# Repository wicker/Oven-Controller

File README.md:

# Composites Curing Oven Controller

For the composites oven team at Portland State. 

v0 - the original schematic representation of the current working breadboard setup.  
v1 - the finished Arduino shield version on a printed circuit board. this works!  
v2 - additions to the v1 Arduino shield design.  
v3 - developing final version for OSHPark order.

**Note**  
On March 6th the oven controller is now being worked on in the mme-capstone repo in the PSAS organization: https://github.com/psas/mme-capstone

### Version 3

v3 is the final version of the oven controller installed on a 4’×8’×4’ curing oven at Portland State in the Mechanical Engineering department.

The blue case is 3D-printed and gets attached to the side of the oven. The electronics are a three-board stack with an Arduino Uno R3 on the bottom; a custom oven control board set up in the middle with screw-in Euroterminals for start switch, relay, and thermocouple wires; and a 1.8” TFT LCD Shield from Adafruit for the display on top.

The display allows the user to program up to nine steps in a temperature profile. Each step lets the user specify a ramp rate, hold temperature, and hold time. Once all the steps are set, the user should set the relay enable switch to ON and then tell the program to begin running the profile.

The program automatically detects which thermocouples are present and uses the temperature as input to a PID loop which controls ramp rate by turning on and off up to four relays which are, for our configuration, controlling two heaters, one fan, and one vent.

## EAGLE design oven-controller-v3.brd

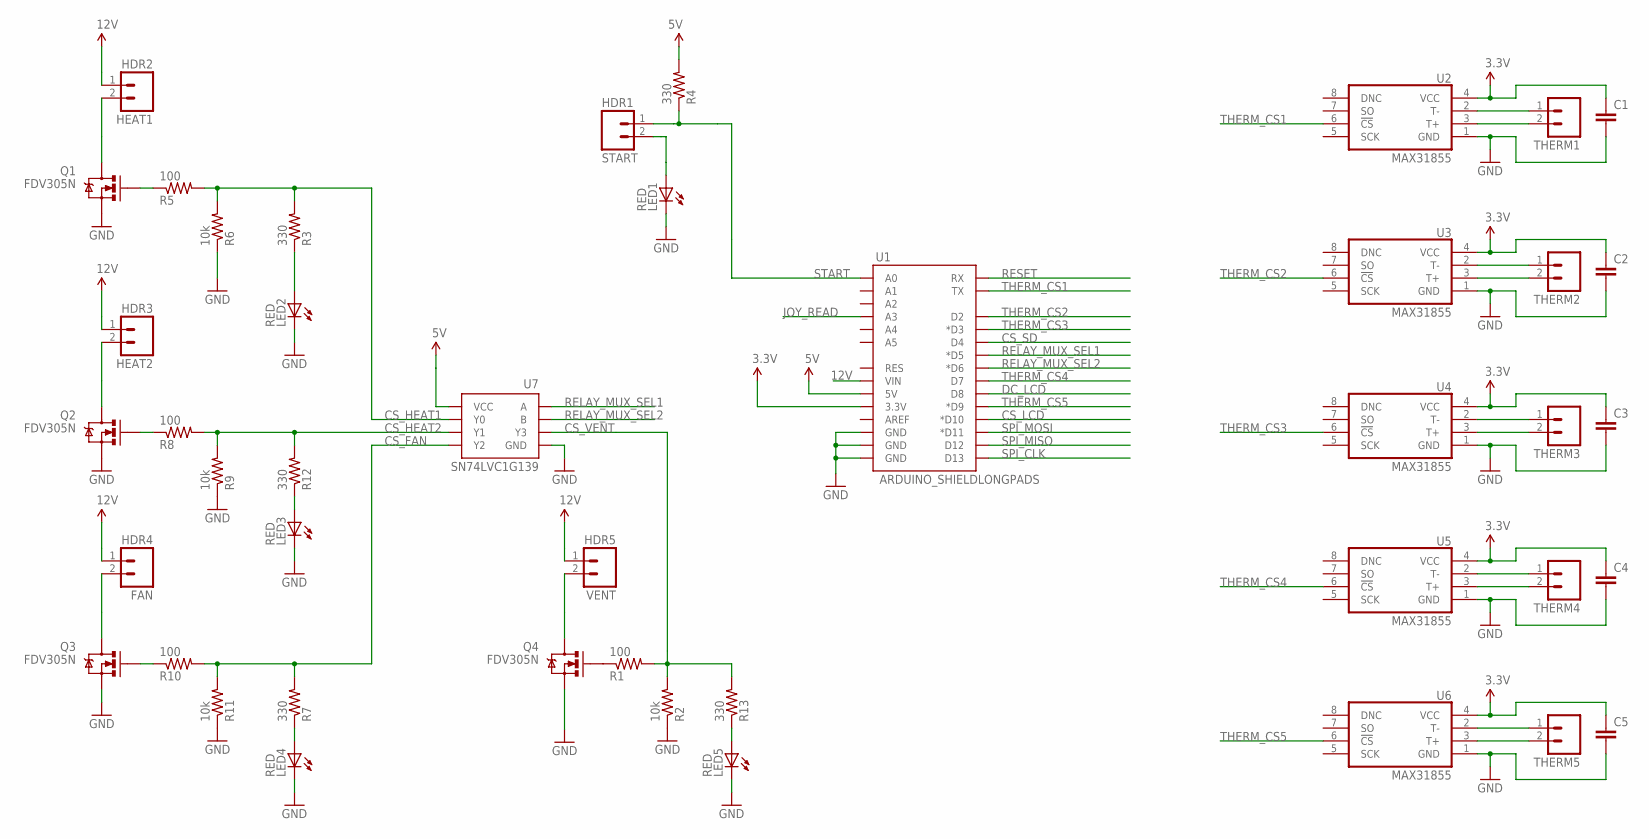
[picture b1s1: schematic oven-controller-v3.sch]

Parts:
C1, C2, C3, C4, C5: C-EUC0603K; C0603K
FAN: HDR4; SCREWTERMINAL-3.5MM-2_LOCK
HEAT1: HDR2; SCREWTERMINAL-3.5MM-2_LOCK
HEAT2: HDR3; SCREWTERMINAL-3.5MM-2_LOCK
LED1, LED2, LED3, LED4, LED5: RED; LED-0603
Q1, Q2, Q3, Q4: FDV305N; SOT23-3
R1, R5, R8, R10: 100; 0603-C-NOSILK
R2, R6, R9, R11: 10k; 0603-C-NOSILK
R3, R4, R7, R12, R13: 330; 0603-C-NOSILK
START: HDR1; SCREWTERMINAL-3.5MM-2_LOCK
THERM1, THERM2, THERM3, THERM4, THERM5: M023.5MM_LOCK; SCREWTERMINAL-3.5MM-2_LOCK
U1: ARDUINO_SHIELDLONGPADS; DUEMILANOVE_SHIELD_LONGPADS
U2, U3, U4, U5, U6: MAX31855; SO-8
U7: SN74LVC1G139; 8LSSOP
VENT: HDR5; SCREWTERMINAL-3.5MM-2_LOCK

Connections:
3.3V: C1.1, C2.1, C3.1, C4.1, C5.1, U1.3.3V, U2.4 (VCC), U3.4 (VCC), U4.4 (VCC), U5.4 (VCC), U6.4 (VCC)
5V: R4.2, U1.5V, U7.P$8 (VCC)
12V: FAN.1, HEAT1.1, HEAT2.1, U1.VIN, VENT.1
CS_FAN: R7.2, R10.2, R11.2, U7.P$5 (Y2)
CS_HEAT1: R3.2, R5.2, R6.2, U7.P$7 (Y0)
CS_HEAT2: R8.2, R9.2, R12.2, U7.P$6 (Y1)
CS_LCD: U1.D10 (*D10)
CS_SD: U1.D4
CS_VENT: R1.2, R2.2, R13.2, U7.P$3 (Y3)
DC_LCD: U1.D8
GND: C1.2, C2.2, C3.2, C4.2, C5.2, LED1.C, LED2.C, LED3.C, LED4.C, LED5.C, Q1.2 (S), Q2.2 (S), Q3.2 (S), Q4.2 (S), R2.1, R6.1, R9.1, R11.1, U1.GND@0 (GND), U1.GND@1 (GND), U1.GND@2 (GND), U2.1 (GND), U3.1 (GND), U4.1 (GND), U5.1 (GND), U6.1 (GND), U7.P$4 (GND)
HDR3: FAN.2, Q3.3 (D)
JOY_READ: U1.A3
unnamed: Q1.1 (G), R5.1
unnamed: Q4.1 (G), R1.1
unnamed: Q4.3 (D), VENT.2
unnamed: HEAT1.2, Q1.3 (D)
unnamed: THERM1.1, U2.2 (T-)
unnamed: THERM1.2, U2.3 (T+)
unnamed: LED2.A, R3.1
unnamed: THERM2.1, U3.2 (T-)
unnamed: LED4.A, R7.1
unnamed: LED1.A, START.2
unnamed: THERM2.2, U3.3 (T+)
unnamed: THERM3.1, U4.2 (T-)
unnamed: THERM3.2, U4.3 (T+)
unnamed: THERM4.1, U5.2 (T-)
unnamed: THERM4.2, U5.3 (T+)
unnamed: THERM5.1, U6.2 (T-)
unnamed: THERM5.2, U6.3 (T+)
unnamed: LED3.A, R12.1
unnamed: LED5.A, R13.1
unnamed: Q2.1 (G), R8.1
unnamed: HEAT2.2, Q2.3 (D)
unnamed: Q3.1 (G), R10.1
RELAY_MUX_SEL1: U1.D5 (*D5), U7.P$1 (A)
RELAY_MUX_SEL2: U1.D6 (*D6), U7.P$2 (B)
RESET: U1.RX
SPI_CLK: U1.D13
SPI_MISO: U1.D12
SPI_MOSI: U1.D11 (*D11)
START: R4.1, START.1, U1.A0
THERM_CS1: U1.TX, U2.6 (!CS)
THERM_CS2: U1.D2, U3.6 (!CS)
THERM_CS3: U1.D3 (*D3), U4.6 (!CS)
THERM_CS4: U1.D7, U5.6 (!CS)
THERM_CS5: U1.D9 (*D9), U6.6 (!CS)

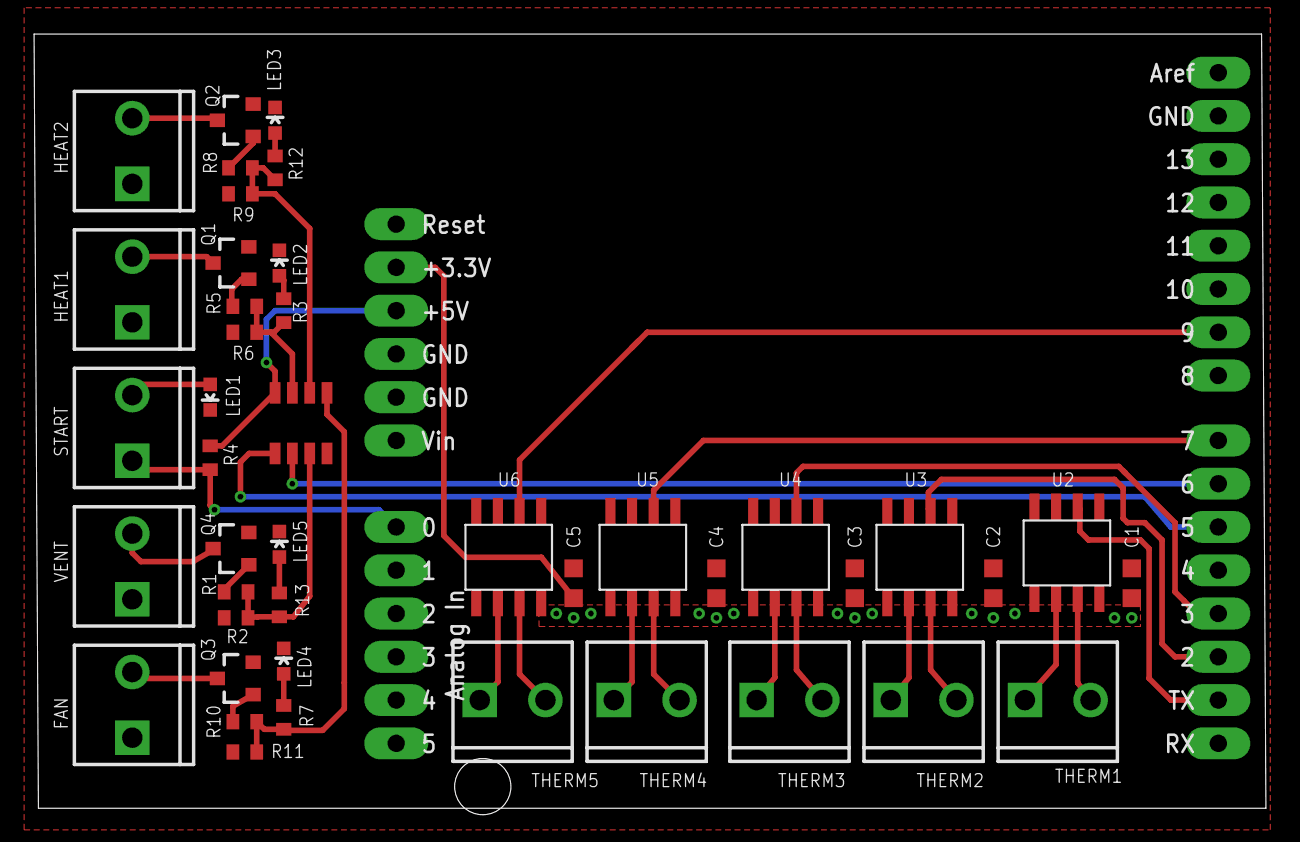
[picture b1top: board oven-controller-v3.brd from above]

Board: 2 copper layers, 72.3 x 45.4 mm, 44 parts (0 on the bottom side), 39 nets.

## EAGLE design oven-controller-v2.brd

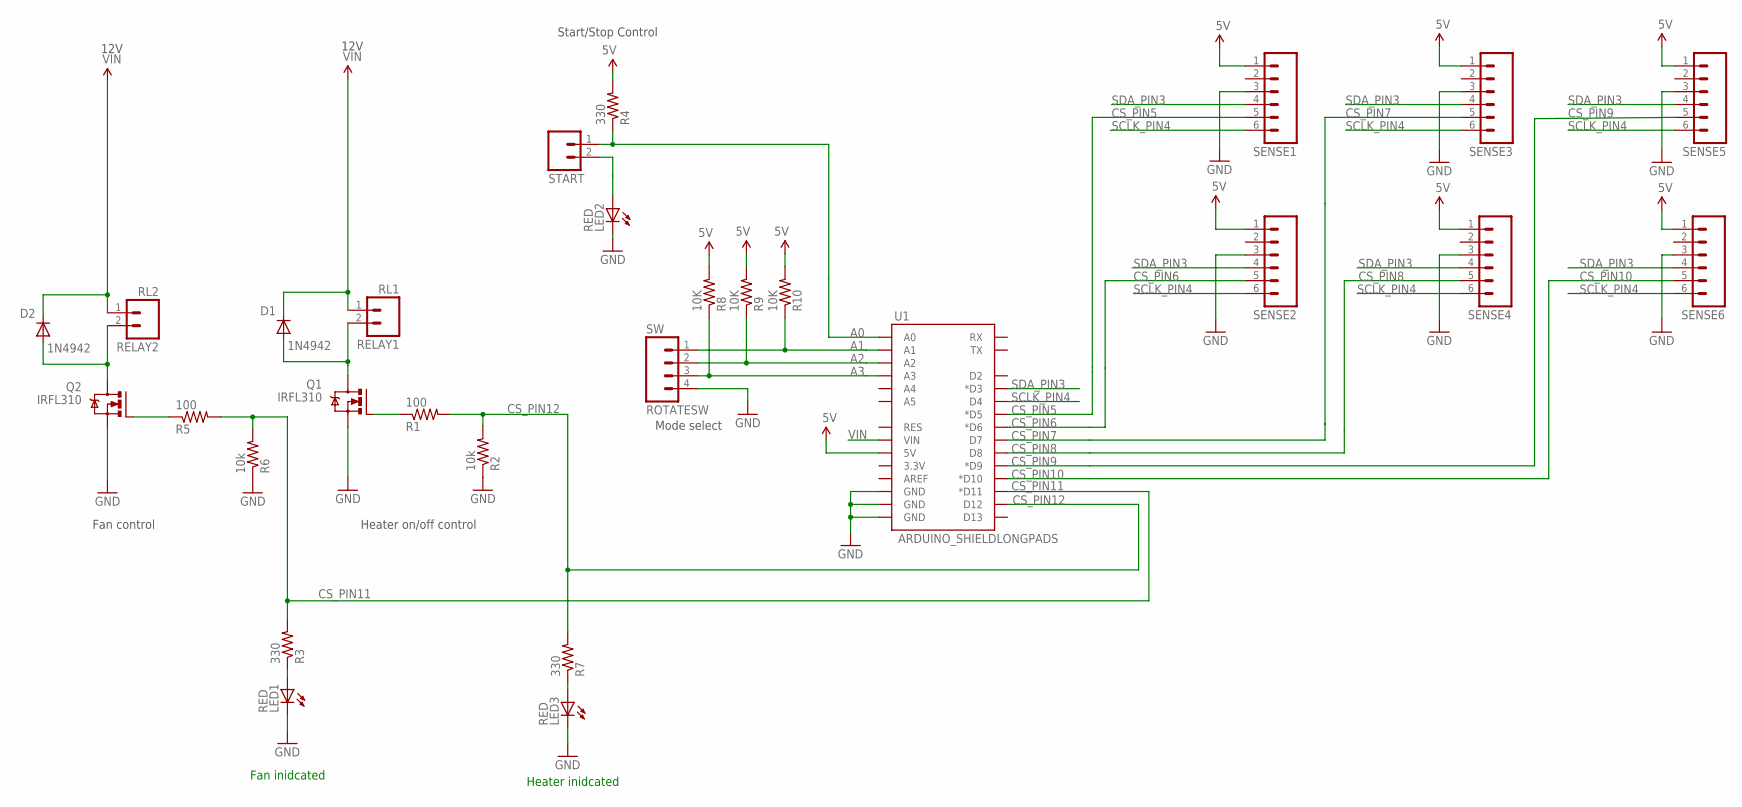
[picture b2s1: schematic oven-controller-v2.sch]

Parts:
D1, D2: 1N4942; DO41-10
LED1, LED2, LED3: RED; LED5MM
Q1, Q2: IRFL310; TO220BV
R1, R5: 100; AXIAL-0.3
R2, R6: 10k; AXIAL-0.3
R3, R4, R7: 330; AXIAL-0.3
R8, R9, R10: 10K; AXIAL-0.3
RELAY1: RL1; SCREWTERMINAL-3.5MM-2_LOCK
RELAY2: RL2; SCREWTERMINAL-3.5MM-2_LOCK
ROTATESW: SW; 1X04_LOCK_LONGPADS
SENSE1, SENSE2, SENSE3, SENSE4, SENSE5, SENSE6: M06LOCK_LONGPADS; 1X06_LOCK_LONGPADS
START: M023.5MM_LOCK; SCREWTERMINAL-3.5MM-2_LOCK
U1: ARDUINO_SHIELDLONGPADS; DUEMILANOVE_SHIELD_LONGPADS

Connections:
5V: R4.P$2 (2), R8.P$2 (2), R9.P$2 (2), R10.P$2 (2), SENSE1.1, SENSE2.1, SENSE3.1, SENSE4.1, SENSE5.1, SENSE6.1, U1.5V
A0: R4.P$1 (1), START.1, U1.A0
A1: R10.P$1 (1), ROTATESW.1, U1.A1
A2: R9.P$1 (1), ROTATESW.2, U1.A2
A3: R8.P$1 (1), ROTATESW.3, U1.A3
CCO: SENSE1.4, SENSE2.4, SENSE3.4, SENSE4.4, SENSE5.4, SENSE6.4, U1.D3 (*D3)
CS_PIN5: SENSE1.5, U1.D5 (*D5)
CS_PIN6: SENSE2.5, U1.D6 (*D6)
CS_PIN7: SENSE3.5, U1.D7
CS_PIN8: SENSE4.5, U1.D8
CS_PIN9: SENSE5.5, U1.D9 (*D9)
CS_PIN10: SENSE6.5, U1.D10 (*D10)
CS_PIN11: R3.P$2 (2), R5.P$2 (2), R6.P$2 (2), U1.D11 (*D11)
CS_PIN12: R1.P$2 (2), R2.P$2 (2), R7.P$2 (2), U1.D12
GND: LED1.K (C), LED2.K (C), LED3.K (C), Q1.S, Q2.S, R2.P$1 (1), R6.P$1 (1), ROTATESW.4, SENSE1.3, SENSE2.3, SENSE3.3, SENSE4.3, SENSE5.3, SENSE6.3, U1.GND@0 (GND), U1.GND@1 (GND), U1.GND@2 (GND)
unnamed: Q2.G, R5.P$1 (1)
unnamed: Q1.G, R1.P$1 (1)
unnamed: D1.A, Q1.D, RELAY1.2
unnamed: D2.A, Q2.D, RELAY2.2
unnamed: LED1.A, R3.P$1 (1)
unnamed: LED3.A, R7.P$1 (1)
unnamed: LED2.A, START.2
SCLK_PIN4: SENSE1.6, SENSE2.6, SENSE3.6, SENSE4.6, SENSE5.6, SENSE6.6, U1.D4
VIN: D1.C, D2.C, RELAY1.1, RELAY2.1, U1.VIN

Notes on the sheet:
Mode select
Heater on/off control
12V
Start/Stop Control
Fan control
Fan inidcated
Heater inidcated

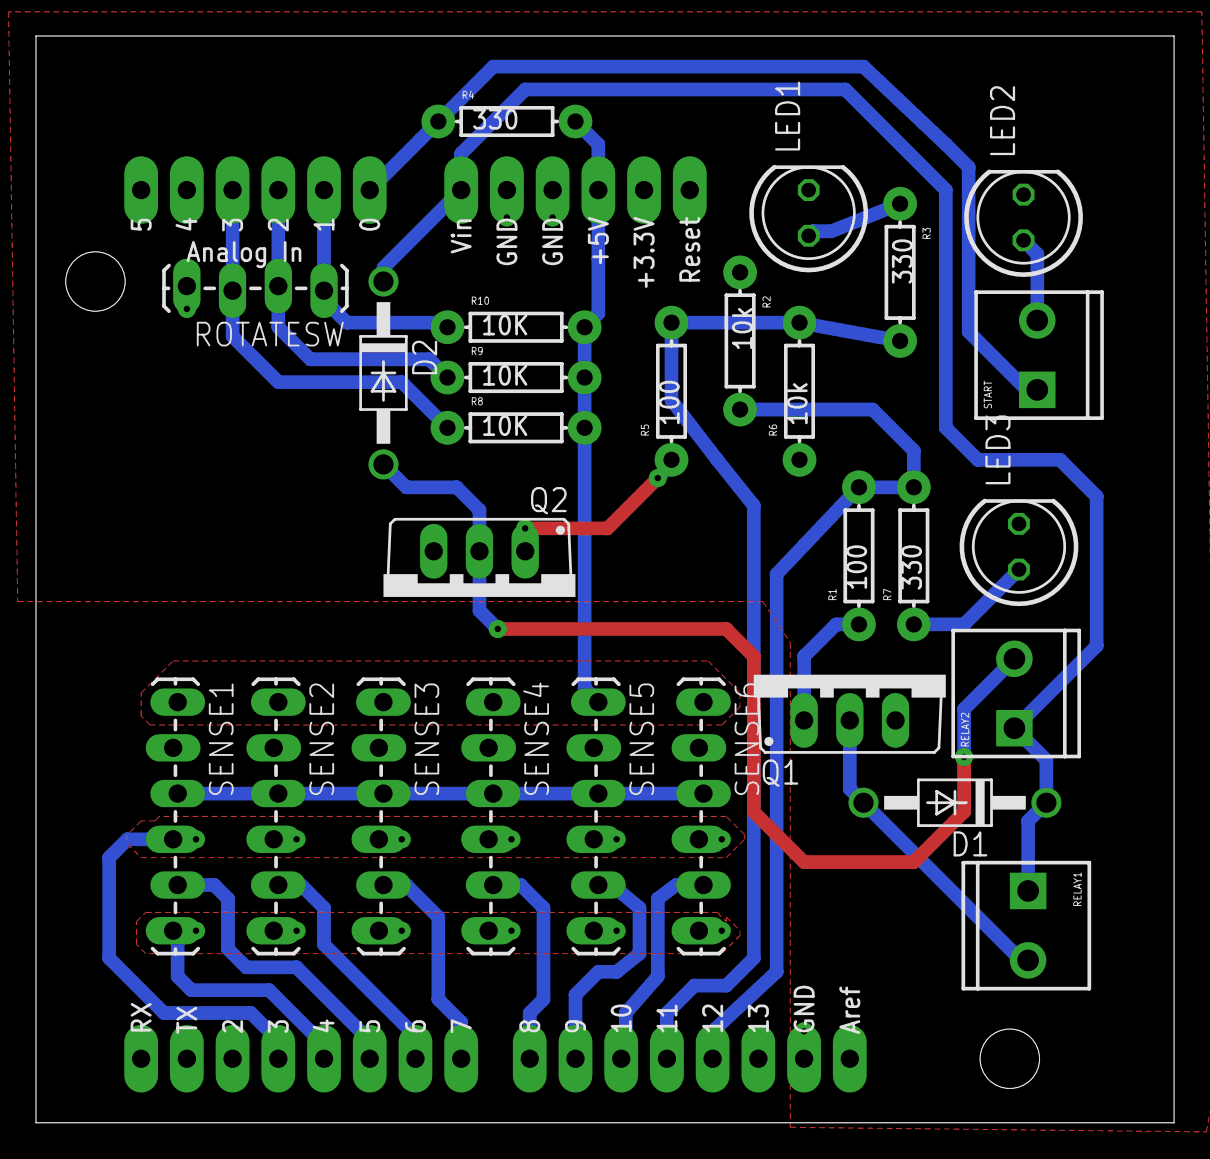
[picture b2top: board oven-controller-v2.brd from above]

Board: 2 copper layers, 63.2 x 60.4 mm, 28 parts (0 on the bottom side), 24 nets.

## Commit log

2014-01-24 First commit.
2014-01-24 All parts on the board, cleaned up layout.
2014-01-25 Schematic and layout done. Connections to Arduino will have to be female headers because we don't have plated vias.
2014-01-25 Dimensions and spacing fixes.
2014-01-27 Fixed for LPKF limitations. Ready for Nystrom via method.
2014-01-27 Final board routed.
2014-01-28 More info on the README.
2014-01-28 Moved it around for better screenshot.
2014-01-28 Added photos.
2014-01-28 Added libraries.
2014-01-28 Removed unnecessary layers.
2014-01-28 Better file names for pics.
2014-01-30 Tung added a fan controlling FET with LED and changed 12V to come through Arduino. We're pretty sure it'll work.
2014-01-30 Started board layout. Made resistors Sparkfun axial footprint.
2014-02-01 Laid out board for v2. ERC and DRC good. Generated Gerbers.
2014-02-01 Uh, definitely update vias before making board.
2014-03-01 Switching to SMT parts. Schematic rough draft. Still needs FETs. Board rough done.
2014-03-02 Removed diodes. FETs now SOT23-3. Schematic and layout done. Ready for review.
2014-03-02 Removed src directory from .gitignore.
2014-03-02 Added Tung's oven control sketches.
2014-03-02 Added v3 note.
2014-03-02 Moved the INO to its own folder so Arduino IDE can read it.
2014-03-02 Updated sketch to reflect new pinouts. It compiles and runs. Not tested with oven board attached, only LCD.
2014-03-02 Changed name of older folder.
2014-03-02 Merged elements of shieldtest we want with updated oven control code. Mostly works. The architecture of the loop needs to change.
2014-03-04 Changed sensors_reading() function to check_temp_sensors() and narrowed focus.
2014-03-04 Wrote handle_joystick() and handle_start_button() as separate functions where start button updates state.
2014-03-04 Merged all four heater functions into one that takes two inputs.
2014-03-04 Added timer reaching maximum to state machine handling function.
2014-03-04 Cleaned up everything, going to build loop() next.
2014-03-04 Changed update_heaters() to take state. Built loop().
2014-03-06 Changing directory structure.
2014-03-06 Changed FET resistors. Fixed routing. Passed ERC and DRC. Ready for review.
2014-03-08 Moved work to MME-CAPSTONE repo in github.com/psas/

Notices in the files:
parts and their libraries:
SparkFun-Boards: Licensing: CC v3.0 Share-Alike You are welcome to use this library for commercial purposes.
